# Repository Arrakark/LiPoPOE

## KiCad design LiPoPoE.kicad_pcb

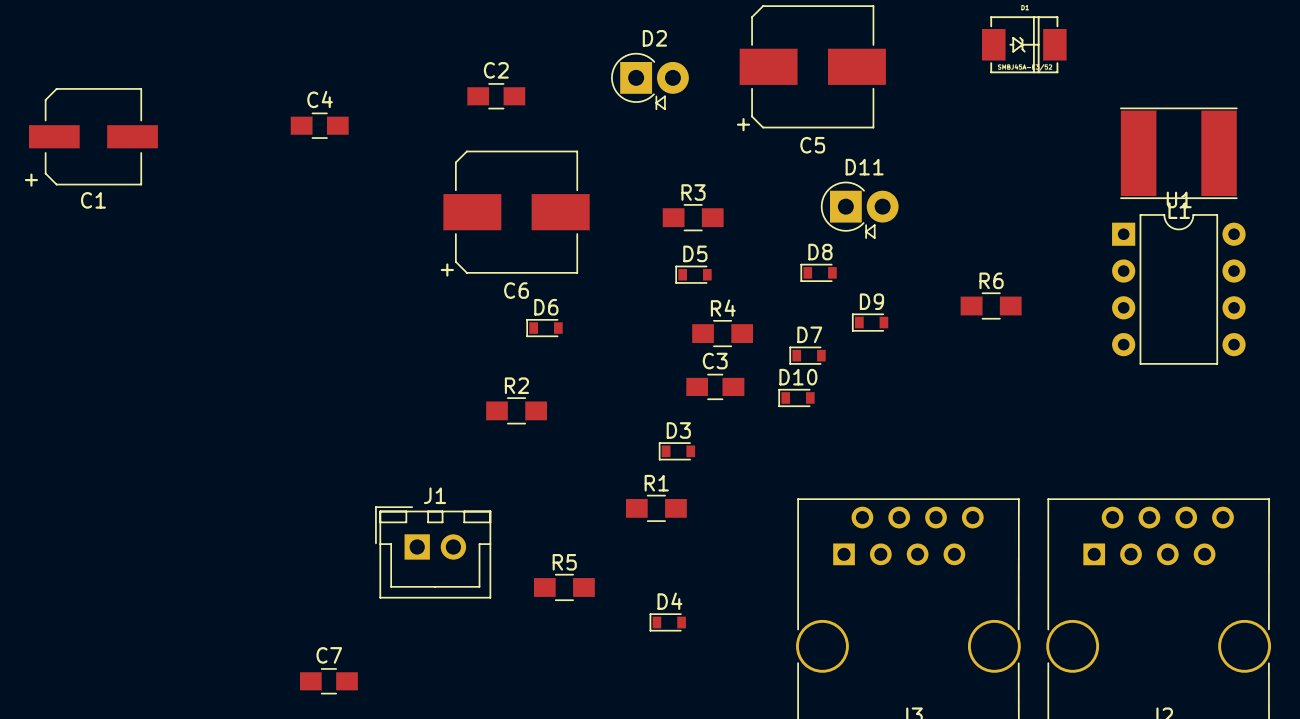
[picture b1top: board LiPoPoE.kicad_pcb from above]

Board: 2 copper layers, 29 parts (0 on the bottom side), 15 nets, no tracks yet.

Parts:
C1: 100uF 35V; CP_Elec_6.3x7.7
C2, C3, C7: 10uF 50V; C_0805_HandSoldering
C4: 50pF 50V; C_0805_HandSoldering
C5, C6: 220uF 35V; CP_Elec_8x10.5
D1: SMBJ45A-E3/52; DO-214AA
D2: 1N4007; D_DO-41_SOD81_P2.54mm_Vertical_AnodeUp
D3, D4, D5, D6, D7, D8, D9, D10: ESDZL5-1F4; D_0603
D11: D_Schottky; D_DO-41_SOD81_P2.54mm_Vertical_AnodeUp
J1: Conn_01x02; JST_XH_B02B-XH-A_02x2.50mm_Straight
J2, J3: RJ45; RJ45_8
L1: 50uH; L_Taiyo-Yuden_NR-60xx_HandSoldering
R1, R2: 0R00; R_0805_HandSoldering
R3: 0R24; R_0805_HandSoldering
R4: 180R; R_0805_HandSoldering
R5: 20k0; R_0805_HandSoldering
R6: 1k10; R_0805_HandSoldering
U1: MC34063A; DIP-8_W7.62mm

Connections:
+24V: C5.1, C6.1, C7.1, D11.1, J3.4, J3.5, R5.1
/RX+: D5.1, D7.1, J2.3, J3.3
/RX-: D6.1, D8.1, J2.6, J3.6
/TX+: D3.1, D9.1, J2.1, J3.1
/TX-: D4.1, D10.1, J2.2, J3.2
GND: C1.2, C2.2, C3.2, C4.2, C5.2, C6.2, C7.2, D1.2, D3.2, D4.2, D5.2, D6.2, J1.2, J3.7, J3.8, R1.2, R2.2, R6.2, U1.2, U1.4
unnamed: C4.1, U1.3
unnamed: D2.2, J1.1
unnamed: D7.2, D8.2
unnamed: D9.2, D10.2
unnamed: D11.2, L1.2, U1.1
unnamed: L1.1, R3.2, R4.2, U1.7
unnamed: R4.1, U1.8
unnamed: R5.2, R6.1, U1.5
VCC: C1.1, C2.1, C3.1, D1.1, D2.1, R3.1, U1.6

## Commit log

2018-05-11 init
2018-05-11 Added pdf and others
